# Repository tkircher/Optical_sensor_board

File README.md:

# Optical_sensor_board
This is a UV/Vis optical sensor board for a wearable

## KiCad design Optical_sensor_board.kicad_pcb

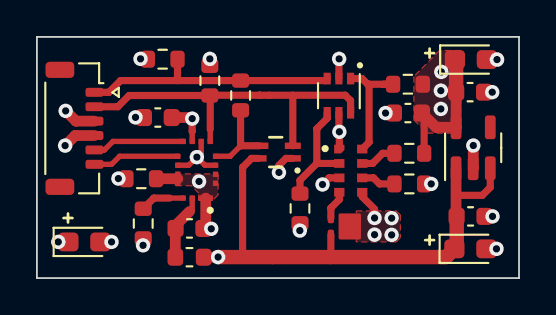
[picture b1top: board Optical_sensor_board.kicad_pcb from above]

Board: 4 copper layers, 26.8 x 13.4 mm, 25 parts (0 on the bottom side), 16 nets.

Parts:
C1, C2, C5: 0.1uF; C_0603_1608Metric
C3, C4: 1uF; C_0603_1608Metric
C6, C7, C8: 4.7uF; CP_EIA-2012-12_Kemet-R
D1: LED; Lumileds-LXZ2
FB1: Ferrite; L_0603_1608Metric
J2: Conn_01x06_Shielded; Hirose_DF52-6S-0.8H_1x06-1MP_P0.80mm_Horizontal
LED1: VEML6040A3OG
Q1: BSS138; SOT-363_SC-70-6
R1: 3.3M; R_0603_1608Metric
R2, R9: 0; R_0603_1608Metric
R3, R4: 10k; R_0603_1608Metric
R5, R6, R7, R8: 2.2k; R_0603_1608Metric
U1: AS7331; AMS-OLGA16
U2: AS7343; AMS-OLGA8
U3: LP3990; SOT-23-5

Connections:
+1V8: C4.1, C5.1, C6.1, Q1.2, Q1.5, R3.2, R5.2, R6.2, U2.1 (VDD), U3.5 (OUT)
+3V3: C1.1, C3.1, C7.1, C8.1, D1.2 (A), FB1.1, J2.4, LED1.4 (VDD), R7.2, R8.2, U1.10 (VDDD), U3.1 (IN), U3.3 (EN)
GNDA: C2.2, R1.2, R2.2, U1.1 (VSSA), U1.2 (VSSA), U1.5 (VSSA), U1.6 (VSSA), U1.15 (VSSA), U1.16 (VSSA)
GNDD: C1.2, C3.2, C4.2, C5.2, C6.2, C7.2, C8.2, D1.TH (Thermal), J2.3, LED1.1 (GND), R2.1, R4.1, U1.7 (A1), U1.11 (VSSD), U1.14 (A0), U2.3 (GND), U2.5 (PGND), U3.2 (GND)
unnamed: D1.1 (K), U2.4 (LDR)
unnamed: R1.1, U1.4 (REXT)
unnamed: C2.1, FB1.2, U1.3 (VDDA)
unnamed: R4.2, U2.6 (GPIO)
unnamed: R3.1, U2.7 (INT)
READY: J2.5, U1.9 (READY)
SCL_1v8: Q1.4, R6.1, U2.2 (SCL)
SCL_3v3: J2.1, Q1.3, R8.1, R9.2
SCL_3v3_jumper: LED1.3 (SCL), R9.1, U1.13 (SCL)
SDA_1v8: Q1.1, R5.1, U2.8 (SDA)
SDA_3v3: J2.2, LED1.2 (SDA), Q1.6, R7.1, U1.12 (SDA)
SYN: J2.6, U1.8 (SYN)

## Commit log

2024-12-22 Added files
2025-01-06 Create LICENSE
